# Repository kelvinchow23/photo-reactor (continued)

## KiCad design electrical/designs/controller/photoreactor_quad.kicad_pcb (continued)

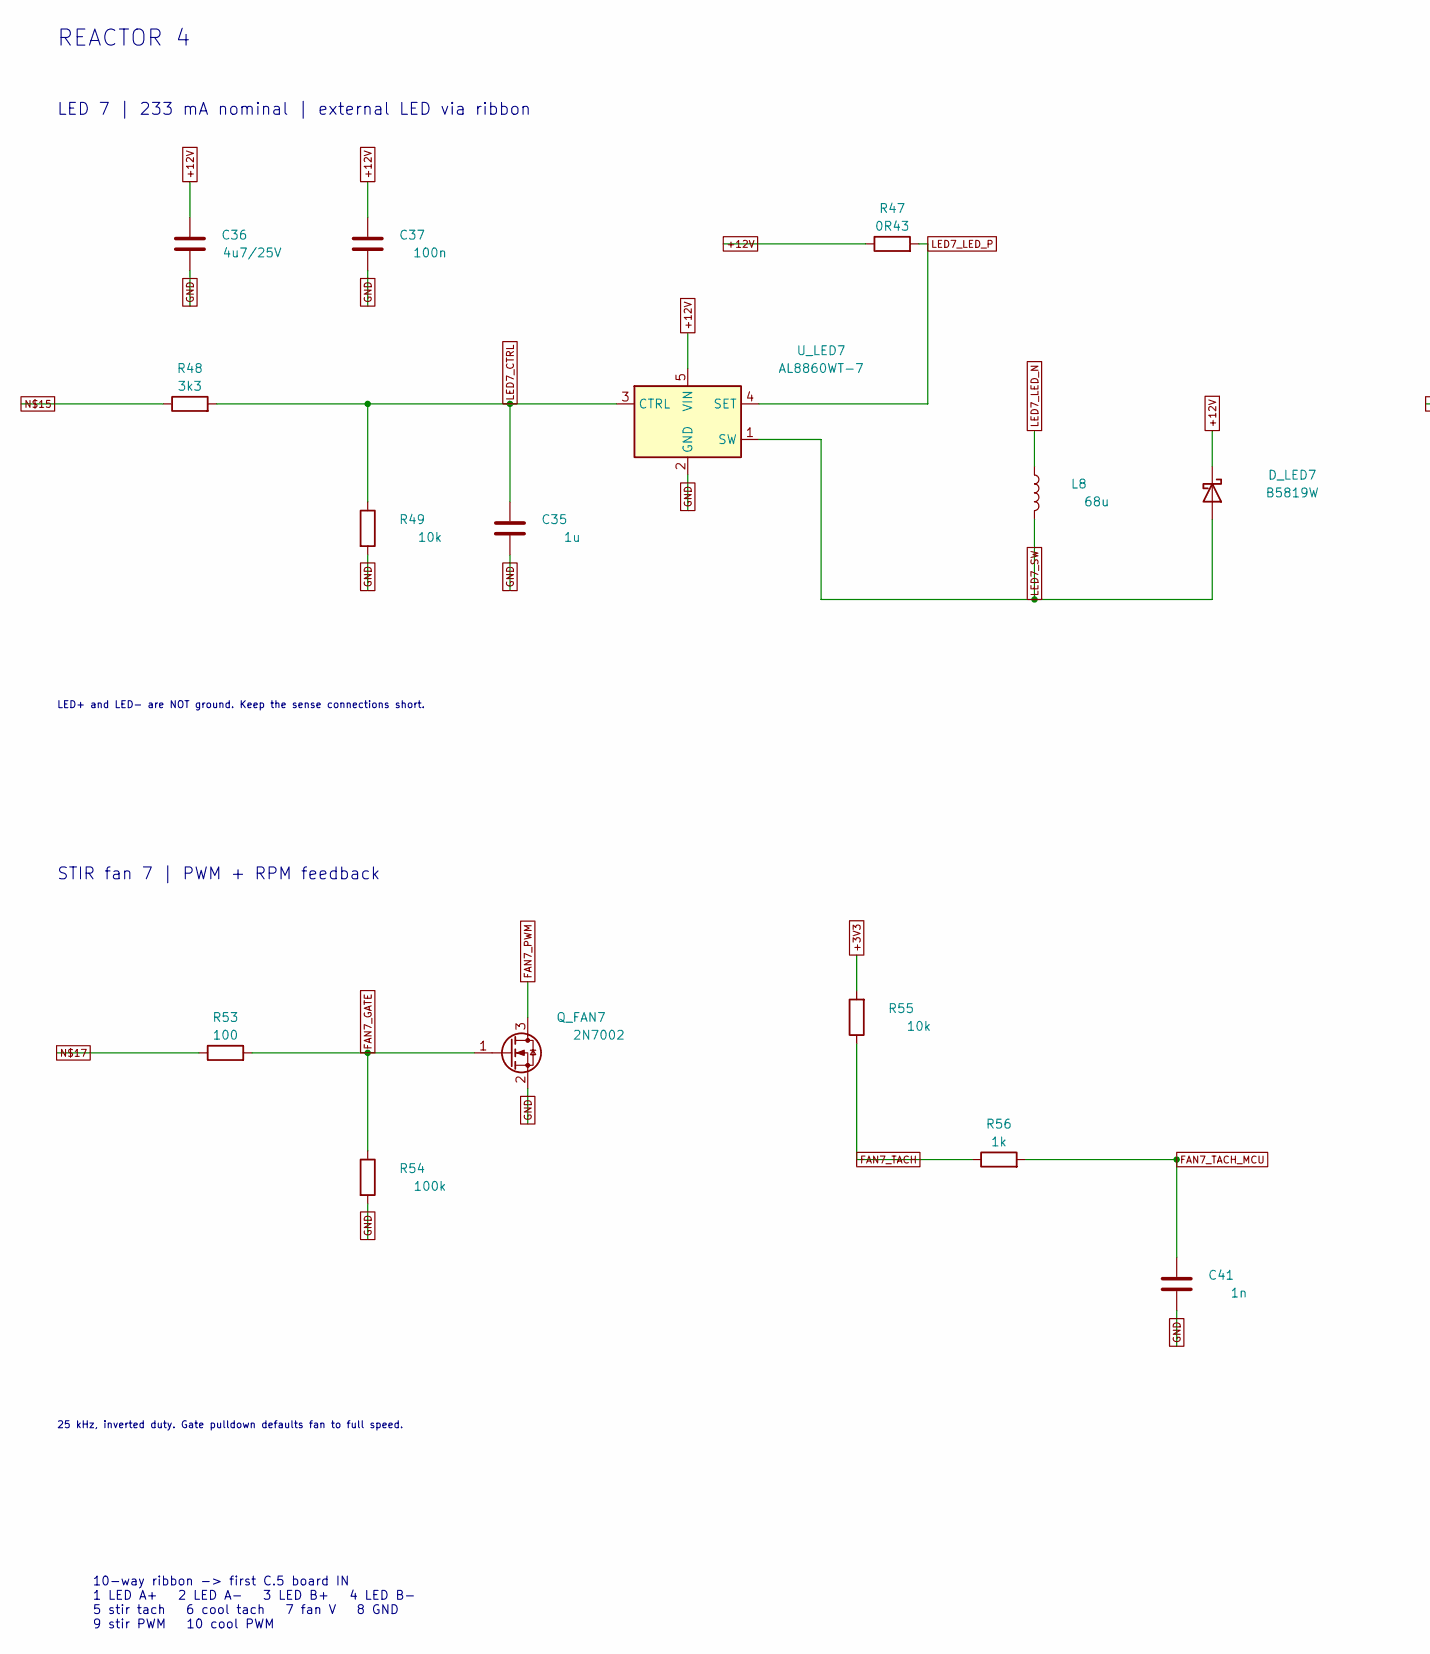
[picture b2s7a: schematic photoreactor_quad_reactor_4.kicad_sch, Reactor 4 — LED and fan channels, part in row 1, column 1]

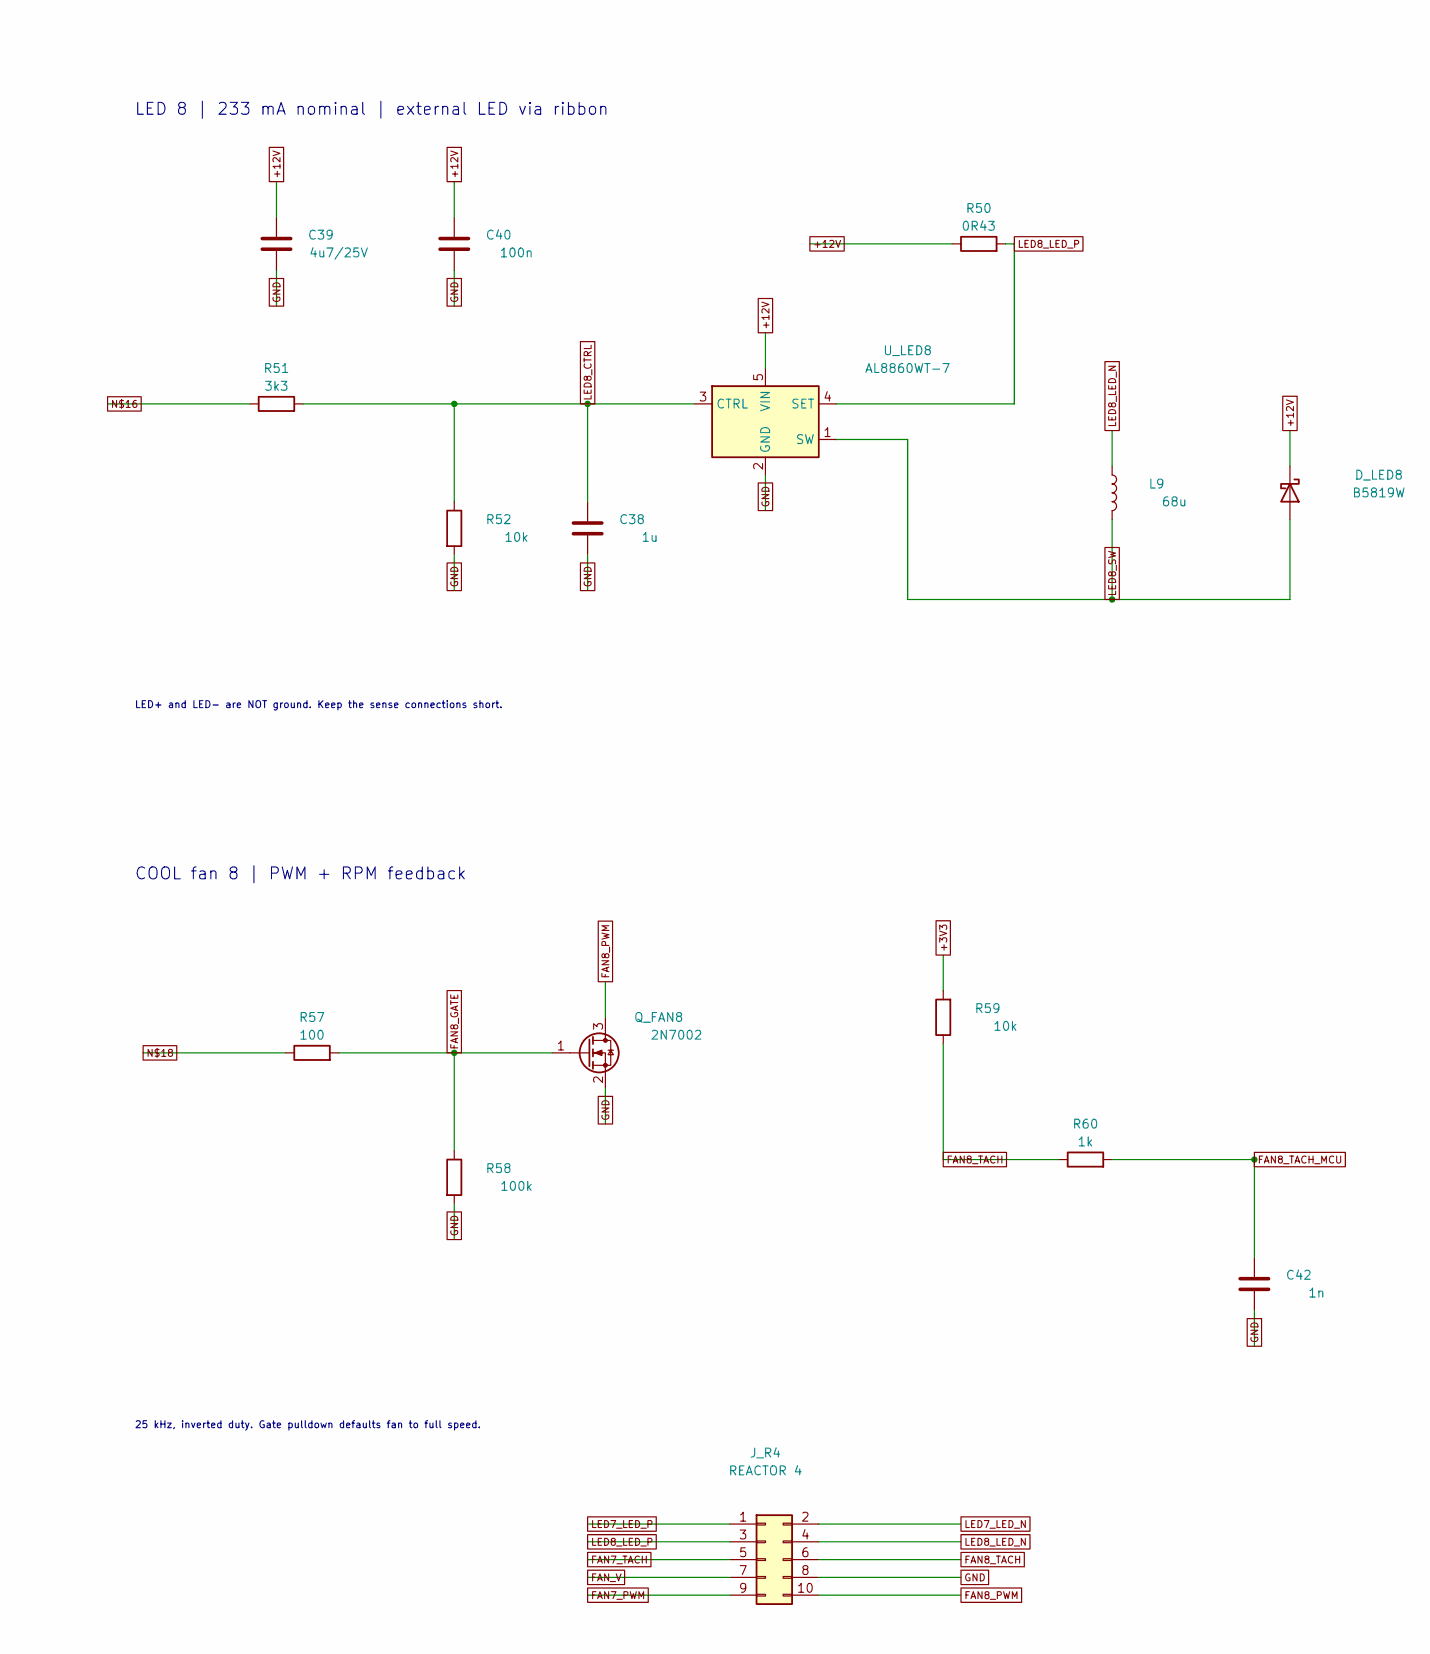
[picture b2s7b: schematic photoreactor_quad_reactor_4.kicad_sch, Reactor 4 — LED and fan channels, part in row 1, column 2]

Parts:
C35, C38: 1u; C_0805_2012Metric; MPN CL21B105KBFNNNE; LCSC C28323
C36, C39: 4u7/25V; C_0805_2012Metric; MPN CL21A475KAQNNNE; LCSC C1779
C37, C40: 100n; C_0805_2012Metric; MPN CC0805KRX7R9BB104; LCSC C49678
C41, C42: 1n; C_0805_2012Metric; MPN CL21B102KCANNNC; LCSC C15177
D_LED7, D_LED8: B5819W; D_SOD-123; MPN B5819W SL
J_R4: REACTOR 4; JXT_IDC2.54_2X5P_A2; MPN JXT-IDC2.54-2X5P-A2
L8, L9: 68u; L_Bourns_SRN6045TA; MPN SRN6045TA-680M
Q_FAN7, Q_FAN8: 2N7002; SOT-23; MPN 2N7002
R47, R50: 0R43; R_1206_3216Metric; MPN CR1206FR430P05R
R48, R51: 3k3; R_0805_2012Metric; MPN 0805W8F3301T5E; LCSC C26010
R49, R52, R55, R59: 10k; R_0805_2012Metric; MPN 0805W8F1002T5E; LCSC C17414
R53, R57: 100; R_0805_2012Metric; MPN 0805W8F1000T5E; LCSC C17408
R54, R58: 100k; R_0805_2012Metric; MPN 0805W8F1003T5E; LCSC C149504
R56, R60: 1k; R_0805_2012Metric; MPN 0805W8F1001T5E; LCSC C17513
U_LED7, U_LED8: AL8860WT-7; SOT-23-5; MPN AL8860WT-7

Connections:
+3V3: R55.2, R59.2; also elsewhere on the board
+12V: C36.1, C37.1, C39.1, C40.1, D_LED7.1 (K), D_LED8.1 (K), R47.1, R50.1, U_LED7.5 (VIN), U_LED8.5 (VIN); also elsewhere on the board
FAN7_GATE: Q_FAN7.1 (G), R53.2, R54.1
FAN7_PWM: J_R4.9, Q_FAN7.3 (D)
FAN7_TACH: J_R4.5, R55.1, R56.1
FAN7_TACH_MCU: C41.1, R56.2; also elsewhere on the board
FAN8_GATE: Q_FAN8.1 (G), R57.2, R58.1
FAN8_PWM: J_R4.10, Q_FAN8.3 (D)
FAN8_TACH: J_R4.6, R59.1, R60.1
FAN8_TACH_MCU: C42.1, R60.2; also elsewhere on the board
FAN_V: J_R4.7; also elsewhere on the board
GND: C35.2, C36.2, C37.2, C38.2, C39.2, C40.2, C41.2, C42.2, J_R4.8, Q_FAN7.2 (S), Q_FAN8.2 (S), R49.2, R52.2, R54.2, R58.2, U_LED7.2 (GND), U_LED8.2 (GND); also elsewhere on the board
LED7_CTRL: C35.1, R48.2, R49.1, U_LED7.3 (CTRL)
LED7_LED_N: J_R4.2, L8.1
LED7_LED_P: J_R4.1, R47.2, U_LED7.4 (SET)
LED7_SW: D_LED7.2 (A), L8.2, U_LED7.1 (SW)
LED8_CTRL: C38.1, R51.2, R52.1, U_LED8.3 (CTRL)
LED8_LED_N: J_R4.4, L9.1
LED8_LED_P: J_R4.3, R50.2, U_LED8.4 (SET)
LED8_SW: D_LED8.2 (A), L9.2, U_LED8.1 (SW)
unnamed 85: R48.1; also elsewhere on the board
unnamed 86: R51.1; also elsewhere on the board
unnamed 87: R53.1; also elsewhere on the board
unnamed 88: R57.1; also elsewhere on the board

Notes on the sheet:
REACTOR 4
LED 7 | 233 mA nominal | external LED via ribbon
LED+ and LED- are NOT ground. Keep the sense connections short.
LED 8 | 233 mA nominal | external LED via ribbon
STIR fan 7 | PWM + RPM feedback
25 kHz, inverted duty. Gate pulldown defaults fan to full speed.
COOL fan 8 | PWM + RPM feedback
10-way ribbon -> first C.5 board IN 1 LED A+ 2 LED A- 3 LED B+ 4 LED B- 5 stir tach 6 cool tach 7 fan V 8 GND 9 stir PWM 10 cool PWM

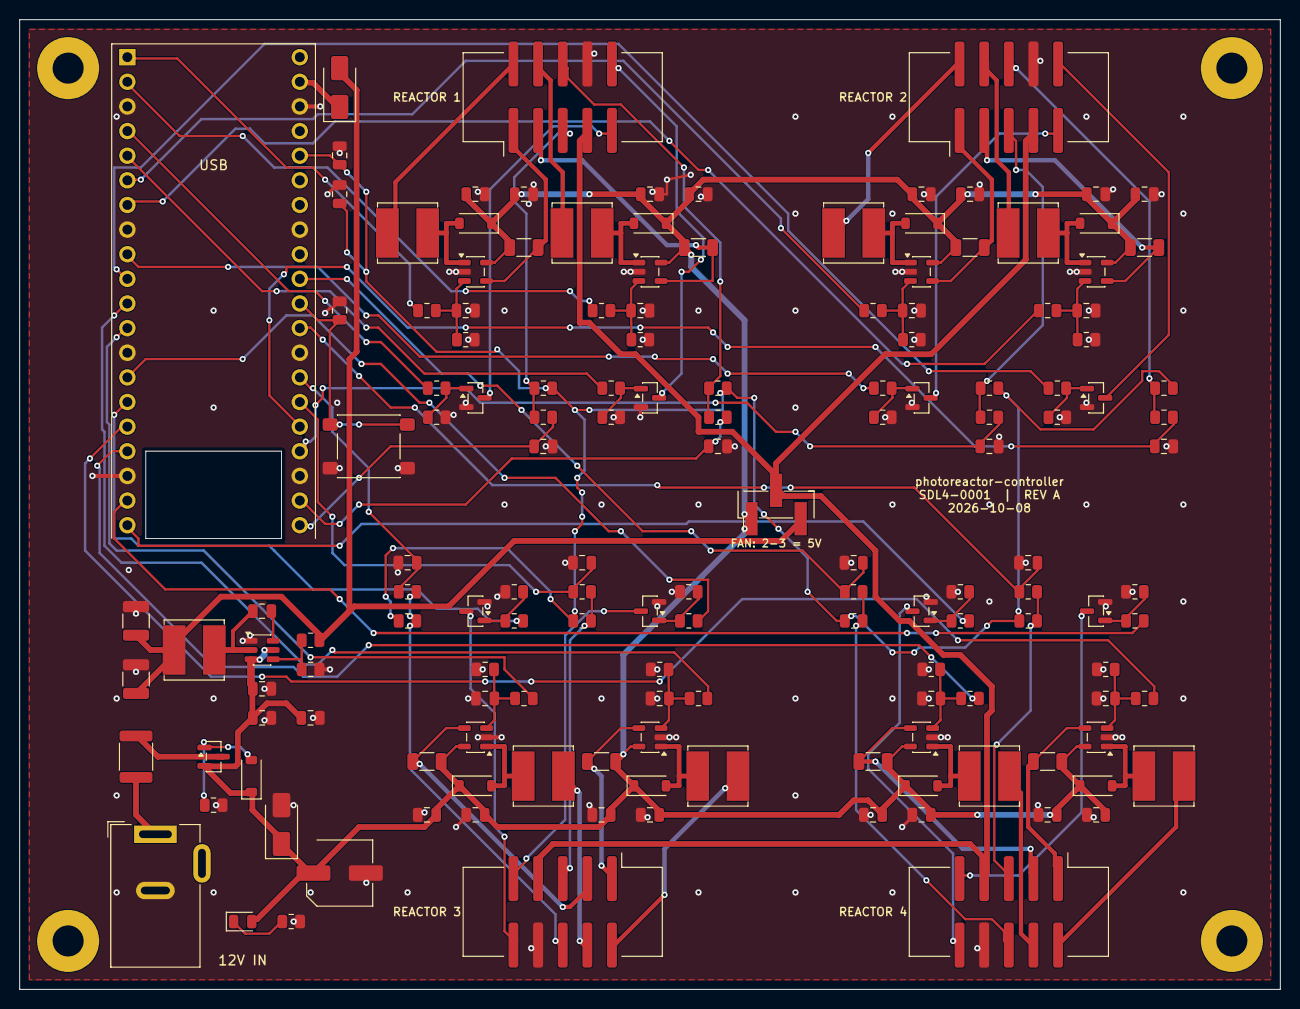
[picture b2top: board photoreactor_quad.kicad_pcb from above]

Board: 2 copper layers, 130.0 x 100.0 mm, 154 parts (0 on the bottom side), 94 nets.

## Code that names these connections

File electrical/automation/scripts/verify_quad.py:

from project_paths import source_path
#!/usr/bin/env python3
"""Connectivity checks for the current four-reactor controller against design intent."""
import re, sys

def tokenize(s): return re.findall(r'\(|\)|"(?:[^"\\]|\\.)*"|[^\s()]+', s)
def parse(tk, i=0):
    out = []
    while i < len(tk):
        t = tk[i]
        if t == '(':  sub, i = parse(tk, i + 1); out.append(sub)
        elif t == ')': return out, i + 1
        else: out.append(t[1:-1] if t.startswith('"') else t); i += 1
    return out, i
def find(n, k): return [x for x in n if isinstance(x, list) and x and x[0] == k]

root, _ = parse(tokenize(open(source_path('photoreactor_quad.net')).read())); root = root[0]
netmap = {}
for n in find(find(root, 'nets')[0], 'net'):
    nodes = find(n, 'node')
    if len(nodes) == 1 and any('no_connect' in f[1] for f in find(nodes[0], 'pintype')):
        continue  # KiCad explicitly marks deliberately unused pins.
    netmap[find(n, 'name')[0][1]] = {(find(nd, 'ref')[0][1], find(nd, 'pin')[0][1])
                                     for nd in find(n, 'node')}
values = {find(c, 'ref')[0][1]: find(c, 'value')[0][1] for c in find(find(root, 'components')[0], 'comp')}
pinnet = {nd: nm for nm, nodes in netmap.items() for nd in nodes}

PIN_TO_GP = {1:0, 2:1, 4:2, 5:3, 6:4, 7:5, 9:6, 10:7, 11:8, 12:9, 14:10, 15:11,
             16:12, 17:13, 19:14, 20:15, 21:16, 22:17, 24:18, 25:19, 26:20,
             27:21, 29:22, 31:26, 32:27, 34:28}

fails = []
def check(cond, msg):
    if cond: print(f'  ok   {msg}')
    else: fails.append(msg); print(f'  FAIL {msg}')

def gp_on(net):
    return [PIN_TO_GP[int(p)] for r, p in netmap.get(net, ()) if r == 'J_PICO' and int(p) in PIN_TO_GP]

print('== LED channels (8) ==')
led_gps = []
for ch in range(1, 9):
    u = f'U_LED{ch}'
    check(pinnet.get((u, '5')) == '+12V', f'{u} VIN on +12V')
    setn, swn, ctrl = pinnet.get((u, '4')), pinnet.get((u, '1')), pinnet.get((u, '3'))
    rs = [r for r, _ in netmap[setn] if r.startswith('R') and any((r, p) in netmap['+12V'] for p in ('1', '2'))]
    check(len(rs) == 1, f'{u} one sense resistor +12V->SET')
    check(len(rs) == 1 and values.get(rs[0]) == '0R43', f'{u} current sense must be 0R43 for XINGLIGHT LED')
    ln = f'LED{ch}_LED_N'
    check(setn == f'LED{ch}_LED_P', f'{u} SET senses LED positive terminal')
    coils = [r for r, _ in netmap.get(swn, ()) if r.startswith('L')]
    check(len(coils) == 1 and
          {pinnet.get((coils[0], p)) for p in ('1', '2')} == {swn, ln},
          f'{u} inductor between LED negative terminal and SW')
    check(pinnet.get((f'D_LED{ch}', '2')) == swn and
          pinnet.get((f'D_LED{ch}', '1')) == '+12V',
          f'{u} catch diode anode SW, cathode +12V')
    check(pinnet.get((u, '2')) == 'GND', f'{u} internal switch ground reference')
    # CTRL is driven through a series R from exactly one Pico pin
    src = [n for r, _ in netmap[ctrl] if r.startswith('R') for n in
           (pinnet.get((r, '1')), pinnet.get((r, '2'))) if n != ctrl]
    gps = [g for n in src for g in gp_on(n)]
    check(len(gps) == 1, f'{u} CTRL fed from one Pico GPIO (GP{gps})')
    led_gps += gps

print('== fan channels (8) ==')
fan_gps, tach_gps = [], []
for ch in range(1, 9):
    q = f'Q_FAN{ch}'
    check(pinnet.get((q, '3')) == f'FAN{ch}_PWM' and pinnet.get((q, '2')) == 'GND', f'{q} drain on PWM, source GND')
    gate_src = [n for r, _ in netmap[f'FAN{ch}_GATE'] if r.startswith('R')
                for n in (pinnet.get((r, '1')), pinnet.get((r, '2'))) if n != f'FAN{ch}_GATE']
    g = [x for n in gate_src for x in gp_on(n)]
    check(len(g) == 1, f'{q} gate from one Pico GPIO (GP{g})')
    fan_gps += g
    t = gp_on(f'FAN{ch}_TACH_MCU')
    check(len(t) == 1, f'FAN{ch} tach on one Pico GPIO (GP{t})')
    tach_gps += t

print('== reactor cables (4) ==')
# the cable pinout must carry exactly this reactor's channels, in the agreed order
for r in range(1, 5):
    la, lb, fs, fc = 2*r-1, 2*r, 2*r-1, 2*r
    want = {1: f'LED{la}_LED_P', 2: f'LED{la}_LED_N',
            3: f'LED{lb}_LED_P', 4: f'LED{lb}_LED_N',
            5: f'FAN{fs}_TACH', 6: f'FAN{fc}_TACH', 7: 'FAN_V', 8: 'GND',
            9: f'FAN{fs}_PWM', 10: f'FAN{fc}_PWM'}
    got = {p: pinnet.get((f'J_R{r}', str(p))) for p in want}
    check(got == want, f'J_R{r} carries reactor {r}: LEDs {la},{lb}  STIR fan {fs}  COOL fan {fc}')

print('== RP2040 PWM resources ==')
pwm = led_gps + fan_gps
chans = [((g >> 1) & 7, g & 1) for g in pwm]
check(len(pwm) == 16, f'16 PWM outputs assigned (got {len(pwm)})')
check(len(set(chans)) == len(chans), 'every PWM output on its own slice channel (none locked together)')
check(not set(tach_gps) & set(pwm), 'tach inputs never share a pin with a PWM output')
check(len(set(pwm + tach_gps)) == len(pwm + tach_gps), 'no GPIO used twice')

print('== power ==')
check(pinnet.get(('Q_REV', '3')) == 'VIN_FUSED' and
      pinnet.get(('Q_REV', '2')) == '+12V' and
      pinnet.get(('Q_REV', '1')) == 'REV_GATE',
      'reverse PMOS: drain input, source protected rail, gate pulldown')
check(pinnet.get(('D_GZ', '1')) == '+12V' and
      pinnet.get(('D_GZ', '2')) == 'REV_GATE', 'gate clamp referenced to PMOS source')
check(pinnet.get(('D_TVS', '1')) == '+12V' and
      pinnet.get(('D_TVS', '2')) == 'GND', 'unidirectional TVS cathode +12V, anode GND')
check(pinnet.get(('J_PICO', '39')) == 'VSYS' and ('D_VSYS', '2') in netmap['+5V'], 'VSYS fed from +5V through D_VSYS')
check({pinnet.get(('JP_FANV', p)) for p in '123'} == {'+12V', 'FAN_V', '+5V'}, 'fan rail jumper selects 12V / 5V')
for a, b in [('+12V', '+5V'), ('+5V', '+3V3'), ('+12V', 'GND'), ('+5V', 'GND'), ('+3V3', 'GND'), ('FAN_V', 'GND')]:
    check(not (netmap.get(a, set()) & netmap.get(b, set())), f'{a} and {b} share no pin')
check(not [n for n, v in netmap.items() if len(v) < 2], 'no dangling single-pin nets')

print(f'\nRESULT: {len(fails)} failure(s)')
for f in fails: print('   -', f)
sys.exit(1 if fails else 0)
